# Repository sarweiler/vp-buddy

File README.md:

# VP Buddy

VP Buddy is a simple video patch bay for patching composite video sources to different destinations. Patching is done via mini jack. There is no normalling for the connections, so what you patch is what you get. It's a passive device, so no need for a power supply. It just connects input and output jacks together, nothing more.

## Yes, but why?

I make [video art](https://rauschfeld.com) with a bunch of old analog video devices, some of them circuit bent, and they mainly use composite video with RCA jacks. I keep forgetting what is connected where and when I saw [a video by All My Friends Are Synths](https://www.youtube.com/watch?v=RH4UdIBQ26o) about a mini jack desktop patch bay that he used with RCA adapters to patch his video devices, I wanted to make a dedicated video patch bay without the need for adapters. Of course, VP Buddy isn't as fancy as the [DF Audio Minibay](https://www.dfaudio.com.au/home) that is shown in the video, but it does the job in helping my forgetful brain see what is going on in my video patch.

## Why mini jack?

Mini jack patch cables are readily available (at your favorite euro rack synthesizer shop, for example) and come in different lengths and colors. They are easier to handle than the often very long RCA cables.

## How to patch

Every top RCA jack is connected to the top mini jack in the corresponding column, every bottom RCA jack is connected the bottom mini jack in the corresponding column. Use this however you like. I have patched all outputs of my devices to the top RCA rows and all inputs of my devices to the bottom RCA rows. You can use the white field at the bottom to indicate what is connected.

## Building

### BOM

- [24 RCA jacks (CUI Devices RCJ-24)](https://www.mouser.com/ProductDetail/490-RCJ-024) (RCJ-21 to RCJ-27 will all work, they're just different colors. Mix and match however you like – RCJ-24 is the classic "video yellow".)
- [24 Thonkiconn jack sockets and 24 nuts](https://www.thonk.co.uk/shop/thonkiconn/)
- For more stability: 10mm standoff screws
- 4 rubber feet

### PCBs

- Get the gerber zips for the bottom PCB and the top PCB.
  - [bottom PCB](https://github.com/sarweiler/vp-buddy/releases/latest/download/gerbers_vp_buddy_bottom.zip)
  - [top PCB](https://github.com/sarweiler/vp-buddy/releases/latest/download/gerbers_vp_buddy_top.zip)
- Upload the zipped files to a PCB manufacturer of your choice, choose a color for the solder mask, and order the PCBs. Default settings should be fine.

### Soldering

- In order to get the mini jack sockets aligned correcly with the top PCB insert the two left most and the two right most mini jacks first. Do not solder them yet. Put the top PCB on and secure the four jack sockets with nuts (not very tight, you will need to unscrew them again).
- Carefully turn your PCB sandwich over and solder the mini jack sockets.
- Unscrew the nuts, take the top PCB off, and and insert all other mini jack sockets. Carefully place the top PCB and put nuts on the four mini jacks that you soldered previously. Turn the PCB sandwich over and solder all mini jack sockets.
- Unscrew the nuts again and take off the top PCB.
- Place all RCA jacks, turn the PCB over (no need to attach the top PCB) and solder all RCA jacks.
- Snip off too long leads protruding at the bottom.
- Install the top PCB with the standoff screws.
- Install the nuts on all mini jacks.
- Install rubber feet, so nothing bad happens, when using VP Buddy on conductive surfaces.
- Done! Happy patching!

## Disclaimer

I'm not an electronics expert, just self taught. Build and use VP Buddy at your own risk.

## License

This work is licensed under [CC-BY-SA 4.0](http://creativecommons.org/licenses/by-sa/4.0/).

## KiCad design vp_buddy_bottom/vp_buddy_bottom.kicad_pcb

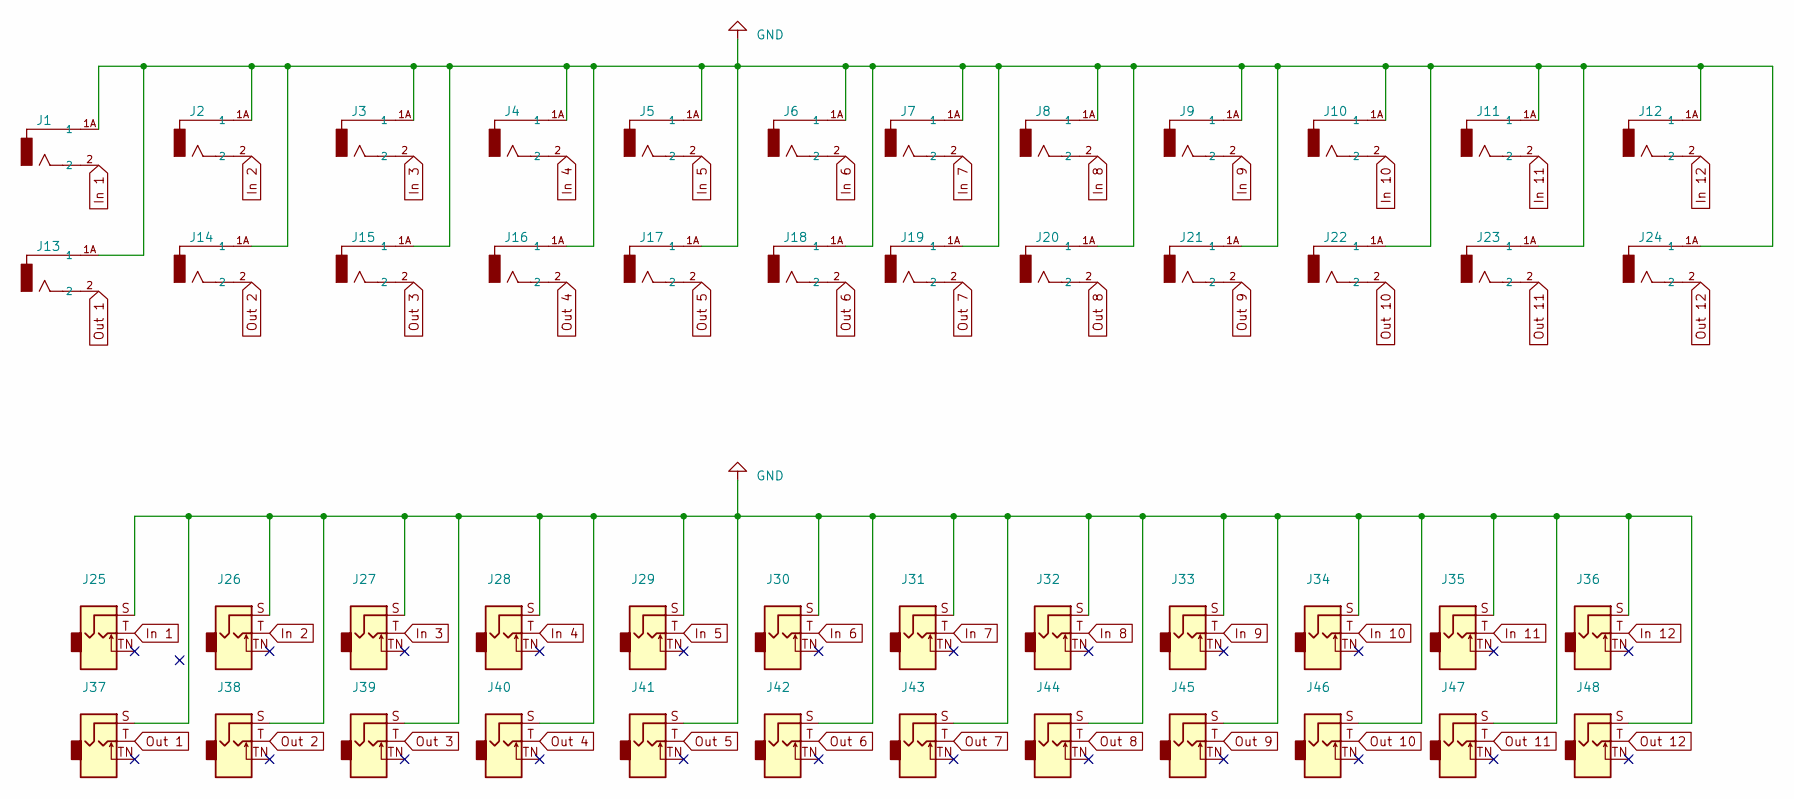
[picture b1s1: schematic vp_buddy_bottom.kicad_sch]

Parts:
J1, J2, J3, J4, J5, J6, J7, J8, J9, J10, J11, J12, J13, J14, J15, J16, J17, J18, J19, J20, J21, J22, J23, J24: Conn_Coaxial; CUI_RCJ-024; PART_REV B
J25, J26, J27, J28, J29, J30, J31, J32, J33, J34, J35, J36, J37, J38, J39, J40, J41, J42, J43, J44, J45, J46, J47, J48: AudioJack2; Jack_3.5mm_QingPu_WQP-PJ398SM_Vertical_CircularHoles

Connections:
GND: J1.1A (1), J1.1B, J2.1A (1), J2.1B, J3.1A (1), J3.1B, J4.1A (1), J4.1B, J5.1A (1), J5.1B, J6.1A (1), J6.1B, J7.1A (1), J7.1B, J8.1A (1), J8.1B, J9.1A (1), J9.1B, J10.1A (1), J10.1B, J11.1A (1), J11.1B, J12.1A (1), J12.1B, J13.1A (1), J13.1B, J14.1A (1), J14.1B, J15.1A (1), J15.1B, J16.1A (1), J16.1B, J17.1A (1), J17.1B, J18.1A (1), J18.1B, J19.1A (1), J19.1B, J20.1A (1), J20.1B, J21.1A (1), J21.1B, J22.1A (1), J22.1B, J23.1A (1), J23.1B, J24.1A (1), J24.1B, J25.S, J26.S, J27.S, J28.S, J29.S, J30.S, J31.S, J32.S, J33.S, J34.S, J35.S, J36.S, J37.S, J38.S, J39.S, J40.S, J41.S, J42.S, J43.S, J44.S, J45.S, J46.S, J47.S, J48.S
In 1: J1.2, J25.T
In 2: J2.2, J26.T
In 3: J3.2, J27.T
In 4: J4.2, J28.T
In 5: J5.2, J29.T
In 6: J6.2, J30.T
In 7: J7.2, J31.T
In 8: J8.2, J32.T
In 9: J9.2, J33.T
In 10: J10.2, J34.T
In 11: J11.2, J35.T
In 12: J12.2, J36.T
Out 1: J13.2, J37.T
Out 2: J14.2, J38.T
Out 3: J15.2, J39.T
Out 4: J16.2, J40.T
Out 5: J17.2, J41.T
Out 6: J18.2, J42.T
Out 7: J19.2, J43.T
Out 8: J20.2, J44.T
Out 9: J21.2, J45.T
Out 10: J22.2, J46.T
Out 11: J23.2, J47.T
Out 12: J24.2, J48.T

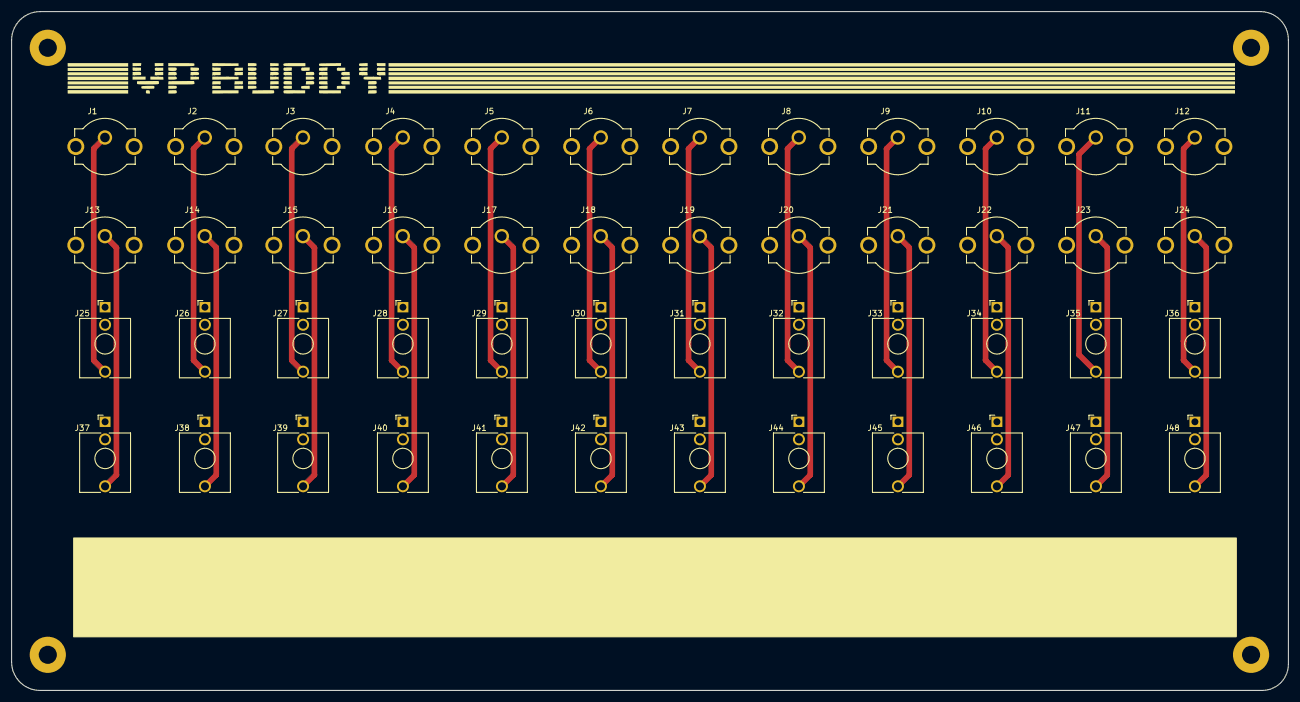
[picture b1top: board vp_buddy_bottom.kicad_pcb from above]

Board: 2 copper layers, 225.7 x 120.0 mm, 48 parts (0 on the bottom side), 25 nets.

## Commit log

2023-05-20 add .gitignore
2023-05-20 add kicad projects
2023-05-20 add README and images
2023-05-20 fix README
2023-05-20 fix download links
2023-05-20 new line
2023-05-20 list
2023-05-20 new photo
